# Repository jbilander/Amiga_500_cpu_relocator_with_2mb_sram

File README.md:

# Amiga 500 CPU Relocator with 2MB Fast SRAM
An Amiga 500 cpu relocator with 2MB sram (four 512 x 8 bit), no autoconfig, use addmem to add memory in Z2 space

***
This project is DEPRECATED, superseded by https://github.com/jbilander/SF500
***

This one I did just for fun, wanted to see if I could add 2 MB fast mem to the amiga 500 with just combinatorial logic IC's. It works well but only runs in the standard 7 MHz speed since DTACK is generated by the normal Amiga bus cycle.

The 2MB can be placed in any of the 16-bit Zorro II space slots with addmem, the jumper needs to be set to any of the four base addresses and correspond to your addmem base address. The addmem command can be found on Aminet if you don't have it in C already.

    addmem 200000 400000
    addmem 400000 600000
    addmem 600000 800000
    addmem 800000 A00000

***

<br /><br />
Testing the relocator with a TF530 that has 2 MB onboard ram. Setting the relocator ram as higher priority memory really slows down the accelelerator since it has to insert wait states to talk to the 7 MHz bus.
<br /><br />

***

Here testing with a TF534 and adding ram at base $600000, works ok but really no need, this was just for fun....

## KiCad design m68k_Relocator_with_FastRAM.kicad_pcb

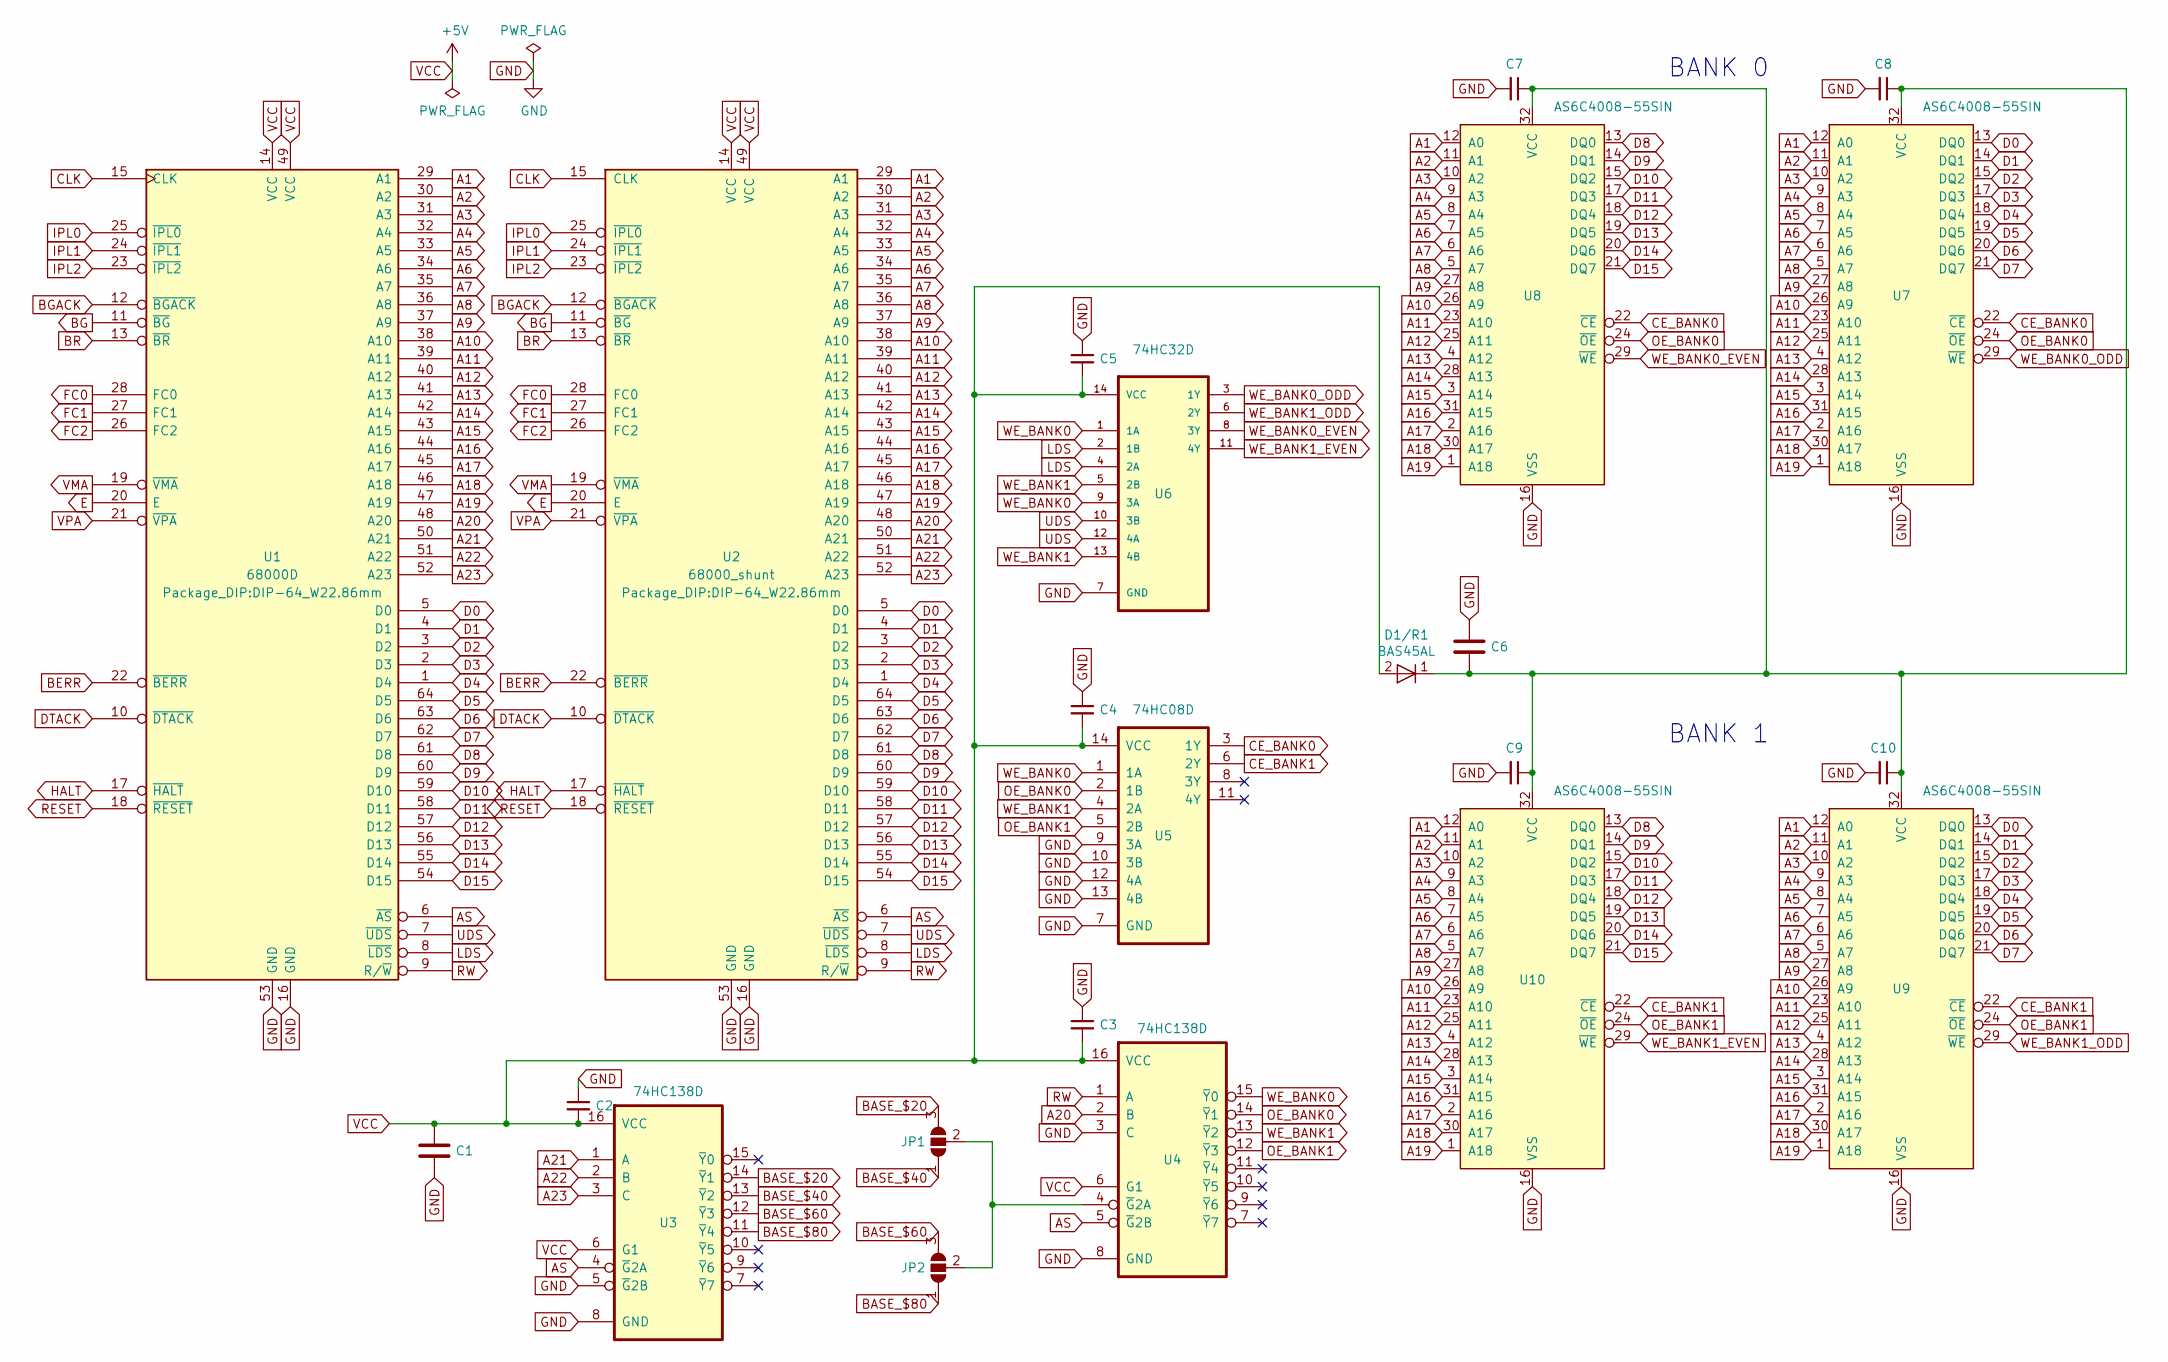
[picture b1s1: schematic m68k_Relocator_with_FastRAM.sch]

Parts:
C1: C; C_1210_3225Metric_Pad1.42x2.65mm_HandSolder
C2, C3, C4, C5: C_Small; C_0805_2012Metric_Pad1.15x1.40mm_HandSolder
C6: C; D_0805_2012Metric_Pad1.15x1.40mm_HandSolder
C7, C8, C9, C10: C_Small; D_0805_2012Metric_Pad1.15x1.40mm_HandSolder
D1/R1: BAS45AL; SOD80C
JP1, JP2: SolderJumper_3_Open; PinHeader_1x03_P2.54mm_Vertical
U1: 68000D; DIP-64_W22.86mm
U2: 68000_shunt; DIP-64_W22.86mm
U3, U4: 74HC138D; SOIC-16_4.55x10.3mm_P1.27mm
U5: 74HC08D; SOIC-14_3.9x8.7mm_P1.27mm
U6: 74HC32D; SOIC-14_3.9x8.7mm_P1.27mm
U7, U8, U9, U10: AS6C4008-55SIN; SSOP-32_11.305x20.495mm_P1.27mm

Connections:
A1: U1.29 (A1), U2.29 (A1), U7.12 (A0), U8.12 (A0), U9.12 (A0), U10.12 (A0)
A2: U1.30 (A2), U2.30 (A2), U7.11 (A1), U8.11 (A1), U9.11 (A1), U10.11 (A1)
A3: U1.31 (A3), U2.31 (A3), U7.10 (A2), U8.10 (A2), U9.10 (A2), U10.10 (A2)
A4: U1.32 (A4), U2.32 (A4), U7.9 (A3), U8.9 (A3), U9.9 (A3), U10.9 (A3)
A5: U1.33 (A5), U2.33 (A5), U7.8 (A4), U8.8 (A4), U9.8 (A4), U10.8 (A4)
A6: U1.34 (A6), U2.34 (A6), U7.7 (A5), U8.7 (A5), U9.7 (A5), U10.7 (A5)
A7: U1.35 (A7), U2.35 (A7), U7.6 (A6), U8.6 (A6), U9.6 (A6), U10.6 (A6)
A8: U1.36 (A8), U2.36 (A8), U7.5 (A7), U8.5 (A7), U9.5 (A7), U10.5 (A7)
A9: U1.37 (A9), U2.37 (A9), U7.27 (A8), U8.27 (A8), U9.27 (A8), U10.27 (A8)
A10: U1.38 (A10), U2.38 (A10), U7.26 (A9), U8.26 (A9), U9.26 (A9), U10.26 (A9)
A11: U1.39 (A11), U2.39 (A11), U7.23 (A10), U8.23 (A10), U9.23 (A10), U10.23 (A10)
A12: U1.40 (A12), U2.40 (A12), U7.25 (A11), U8.25 (A11), U9.25 (A11), U10.25 (A11)
A13: U1.41 (A13), U2.41 (A13), U7.4 (A12), U8.4 (A12), U9.4 (A12), U10.4 (A12)
A14: U1.42 (A14), U2.42 (A14), U7.28 (A13), U8.28 (A13), U9.28 (A13), U10.28 (A13)
A15: U1.43 (A15), U2.43 (A15), U7.3 (A14), U8.3 (A14), U9.3 (A14), U10.3 (A14)
A16: U1.44 (A16), U2.44 (A16), U7.31 (A15), U8.31 (A15), U9.31 (A15), U10.31 (A15)
A17: U1.45 (A17), U2.45 (A17), U7.2 (A16), U8.2 (A16), U9.2 (A16), U10.2 (A16)
A18: U1.46 (A18), U2.46 (A18), U7.30 (A17), U8.30 (A17), U9.30 (A17), U10.30 (A17)
A19: U1.47 (A19), U2.47 (A19), U7.1 (A18), U8.1 (A18), U9.1 (A18), U10.1 (A18)
A20: U1.48 (A20), U2.48 (A20), U4.2 (B)
A21: U1.50 (A21), U2.50 (A21), U3.1 (A)
A22: U1.51 (A22), U2.51 (A22), U3.2 (B)
A23: U1.52 (A23), U2.52 (A23), U3.3 (C)
AS: U1.6 (~AS), U2.6 (~AS), U3.4 (~G~2A), U4.5 (~G~2B)
BASE_$20: JP1.3 (B), U3.14 (~Y~1)
BASE_$40: JP1.1 (A), U3.13 (~Y~2)
BASE_$60: JP2.3 (B), U3.12 (~Y~3)
BASE_$80: JP2.1 (A), U3.11 (~Y~4)
BERR: U1.22 (~BERR), U2.22 (~BERR)
BG: U1.11 (~BG), U2.11 (~BG)
BGACK: U1.12 (~BGACK), U2.12 (~BGACK)
BR: U1.13 (~BR), U2.13 (~BR)
CE_BANK0: U5.3 (1Y), U7.22 (~CE), U8.22 (~CE)
CE_BANK1: U5.6 (2Y), U9.22 (~CE), U10.22 (~CE)
CLK: U1.15 (CLK), U2.15 (CLK)
D0: U1.5 (D0), U2.5 (D0), U7.13 (DQ0), U9.13 (DQ0)
D1: U1.4 (D1), U2.4 (D1), U7.14 (DQ1), U9.14 (DQ1)
D2: U1.3 (D2), U2.3 (D2), U7.15 (DQ2), U9.15 (DQ2)
D3: U1.2 (D3), U2.2 (D3), U7.17 (DQ3), U9.17 (DQ3)
D4: U1.1 (D4), U2.1 (D4), U7.18 (DQ4), U9.18 (DQ4)
D5: U1.64 (D5), U2.64 (D5), U7.19 (DQ5), U9.19 (DQ5)
D6: U1.63 (D6), U2.63 (D6), U7.20 (DQ6), U9.20 (DQ6)
D7: U1.62 (D7), U2.62 (D7), U7.21 (DQ7), U9.21 (DQ7)
D8: U1.61 (D8), U2.61 (D8), U8.13 (DQ0), U10.13 (DQ0)
D9: U1.60 (D9), U2.60 (D9), U8.14 (DQ1), U10.14 (DQ1)
D10: U1.59 (D10), U2.59 (D10), U8.15 (DQ2), U10.15 (DQ2)
D11: U1.58 (D11), U2.58 (D11), U8.17 (DQ3), U10.17 (DQ3)
D12: U1.57 (D12), U2.57 (D12), U8.18 (DQ4), U10.18 (DQ4)
D13: U1.56 (D13), U2.56 (D13), U8.19 (DQ5), U10.19 (DQ5)
D14: U1.55 (D14), U2.55 (D14), U8.20 (DQ6), U10.20 (DQ6)
D15: U1.54 (D15), U2.54 (D15), U8.21 (DQ7), U10.21 (DQ7)
DTACK: U1.10 (~DTACK), U2.10 (~DTACK)
E: U1.20 (E), U2.20 (E)
FC0: U1.28 (FC0), U2.28 (FC0)
FC1: U1.27 (FC1), U2.27 (FC1)
FC2: U1.26 (FC2), U2.26 (FC2)
GND: C1.2, C2.1, C3.1, C4.1, C5.1, C6.1, C7.2, C8.2, C9.2, C10.2, U1.16 (GND), U1.53 (GND), U2.16 (GND), U2.53 (GND), U3.5 (~G~2B), U3.8 (GND), U4.3 (C), U4.8 (GND), U5.7 (GND), U5.9 (3A), U5.10 (3B), U5.12 (4A), U5.13 (4B), U6.7 (GND), U7.16 (VSS), U8.16 (VSS), U9.16 (VSS), U10.16 (VSS)
HALT: U1.17 (~HALT), U2.17 (~HALT)
IPL0: U1.25 (~IPL0), U2.25 (~IPL0)
IPL1: U1.24 (~IPL1), U2.24 (~IPL1)
IPL2: U1.23 (~IPL2), U2.23 (~IPL2)
LDS: U1.8 (~LDS), U2.8 (~LDS), U6.2 (1B), U6.4 (2A)
unnamed: C6.2, C7.1, C8.1, C9.1, C10.1, D1/R1.1, U7.32 (VCC), U8.32 (VCC), U9.32 (VCC), U10.32 (VCC)
unnamed: JP1.2 (C), JP2.2 (C), U4.4 (~G~2A)
OE_BANK0: U4.14 (~Y~1), U5.2 (1B), U7.24 (~OE), U8.24 (~OE)
OE_BANK1: U4.12 (~Y~3), U5.5 (2B), U9.24 (~OE), U10.24 (~OE)
RESET: U1.18 (~RESET), U2.18 (~RESET)
RW: U1.9 (R/~W), U2.9 (R/~W), U4.1 (A)
UDS: U1.7 (~UDS), U2.7 (~UDS), U6.10 (3B), U6.12 (4A)
VCC: C1.1, C2.2, C3.2, C4.2, C5.2, D1/R1.2, U1.14 (VCC), U1.49 (VCC), U2.14 (VCC), U2.49 (VCC), U3.6 (G1), U3.16 (VCC), U4.6 (G1), U4.16 (VCC), U5.14 (VCC), U6.14 (VCC)
VMA: U1.19 (~VMA), U2.19 (~VMA)
VPA: U1.21 (~VPA), U2.21 (~VPA)
WE_BANK0: U4.15 (~Y~0), U5.1 (1A), U6.1 (1A), U6.9 (3A)
WE_BANK0_EVEN: U6.8 (3Y), U8.29 (~WE)
WE_BANK0_ODD: U6.3 (1Y), U7.29 (~WE)
WE_BANK1: U4.13 (~Y~2), U5.4 (2A), U6.5 (2B), U6.13 (4B)
WE_BANK1_EVEN: U6.11 (4Y), U10.29 (~WE)
WE_BANK1_ODD: U6.6 (2Y), U9.29 (~WE)

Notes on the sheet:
BANK 1
BANK 0

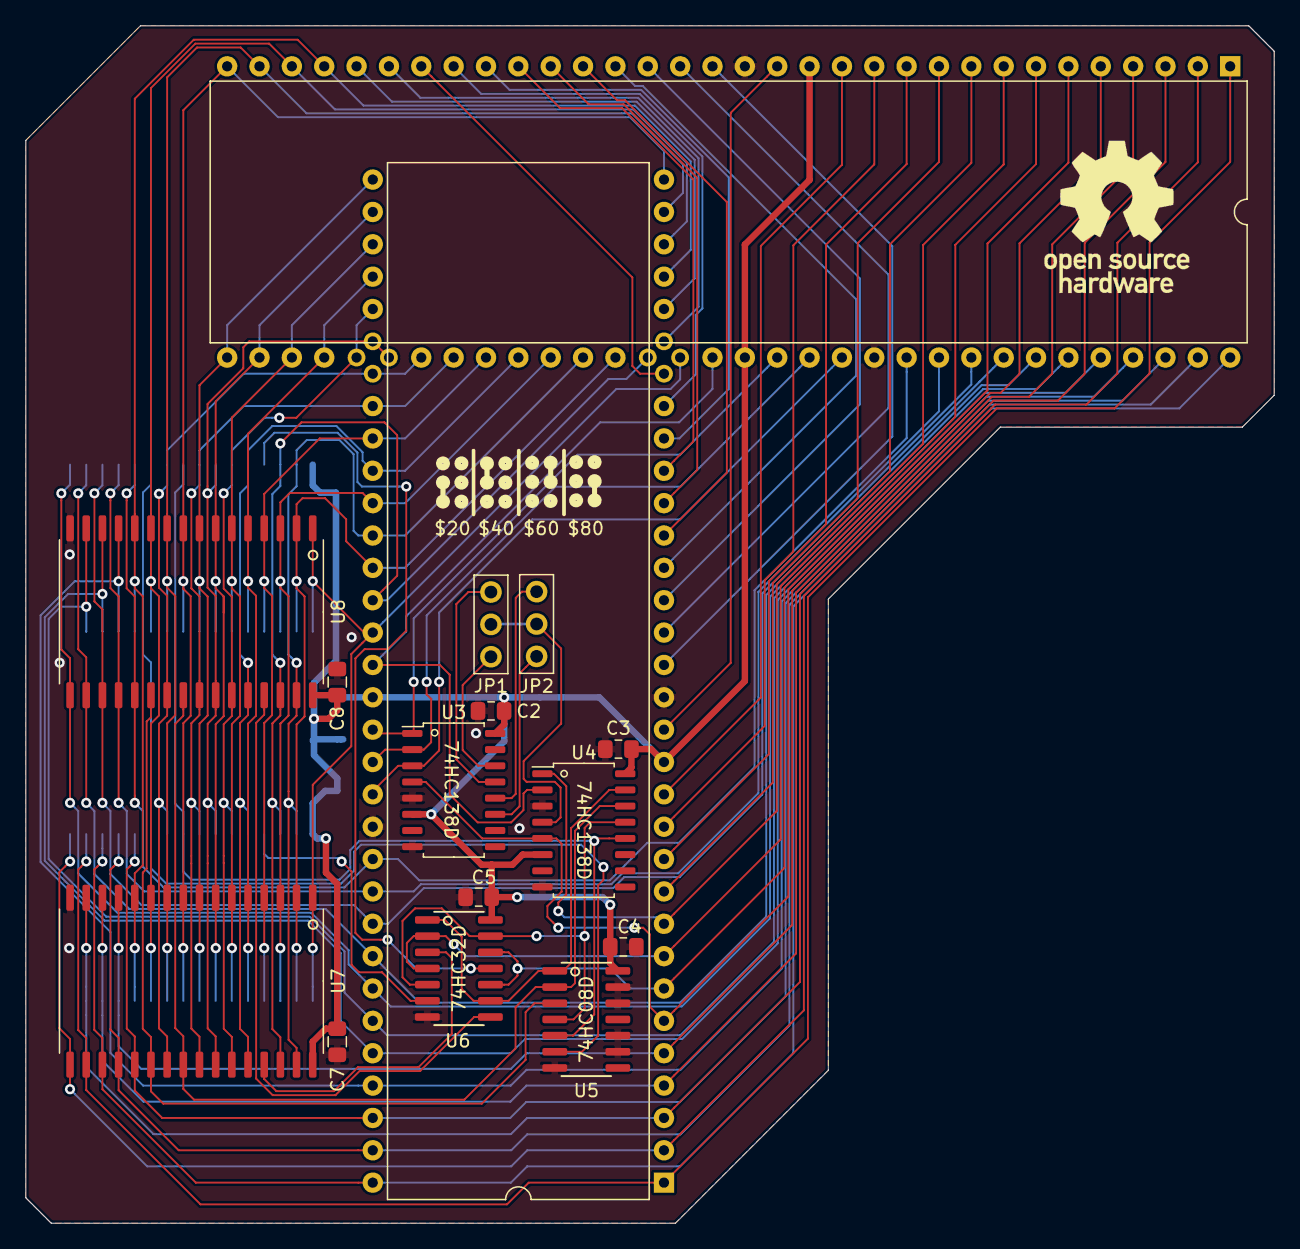
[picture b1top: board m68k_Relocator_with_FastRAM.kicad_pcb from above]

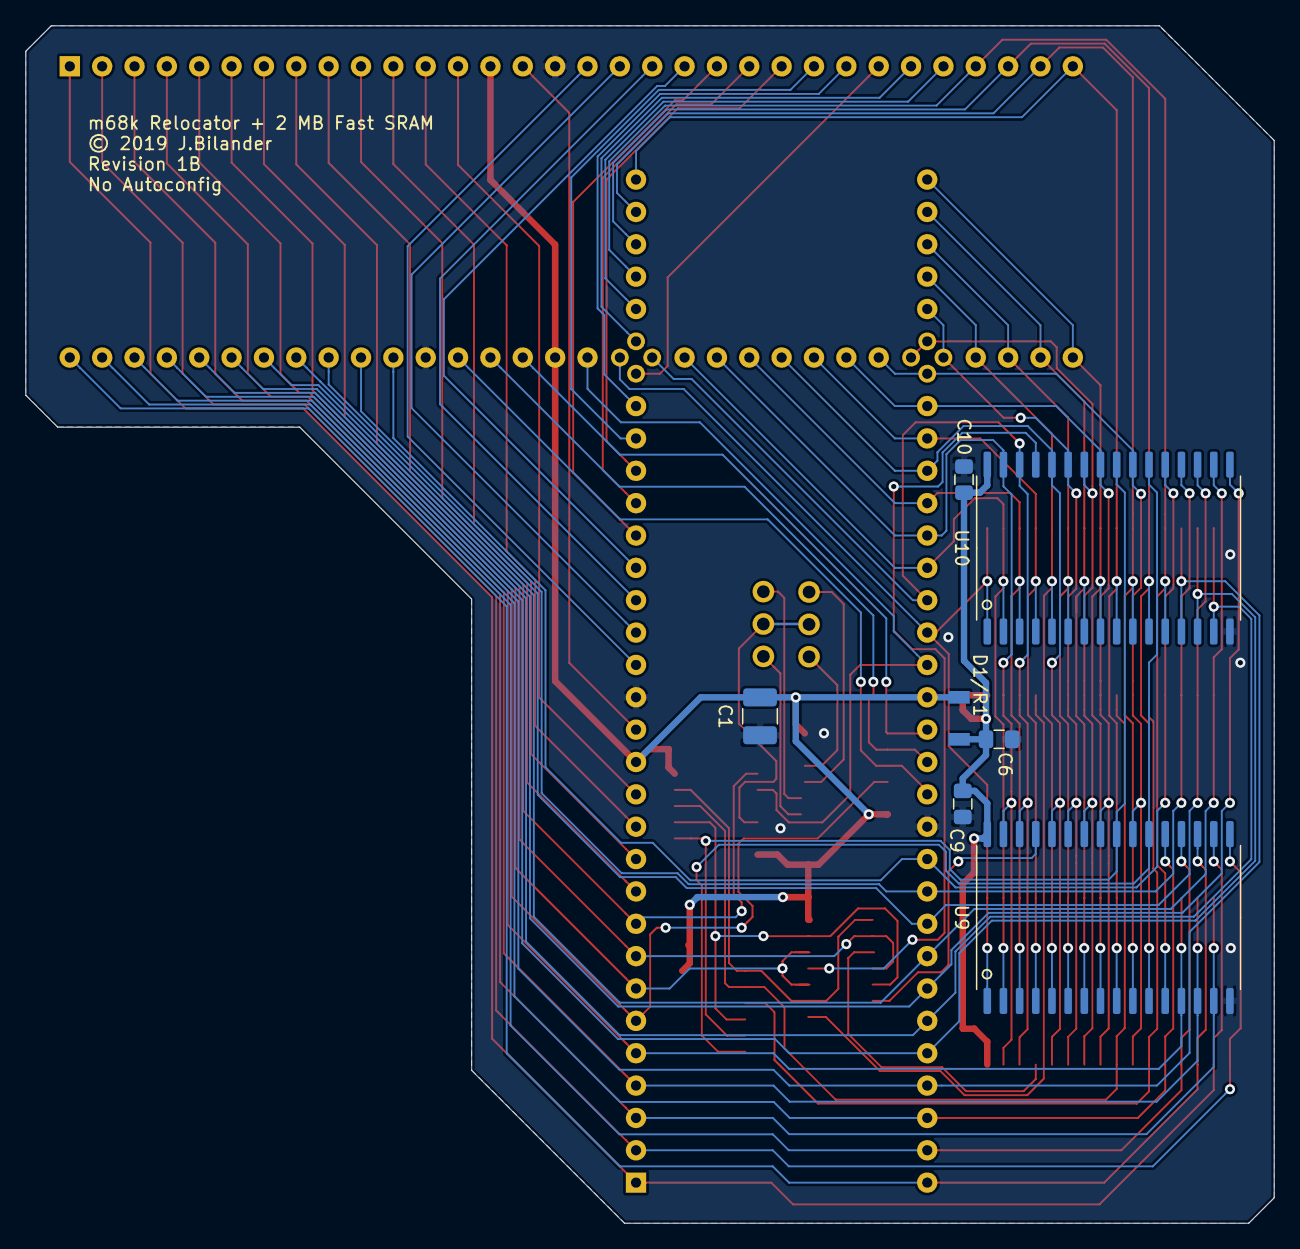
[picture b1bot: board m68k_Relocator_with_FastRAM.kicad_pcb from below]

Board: 2 copper layers, 98.0 x 94.0 mm, 23 parts (7 on the bottom side), 78 nets.

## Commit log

2020-02-27 edited gitignore
2020-02-27 added images
2020-02-27 added source files

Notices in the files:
m68k_Relocator_with_FastRAM.kicad_pcb:
© 2019 J.Bilander
